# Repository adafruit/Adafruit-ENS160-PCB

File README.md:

## Adafruit ENS160 MOX Gas Sensor PCB

<a href="http://www.adafruit.com/products/5606"><br/>
Click here to purchase one from the Adafruit shop</a>

PCB files for the Adafruit ENS160 MOX Gas Sensor. 

Format is EagleCAD schematic and board layout
* https://www.adafruit.com/product/5606

### Description

*sniff* *sniff* ... do you smell that? No need to stick your nose into a carton of milk anymore, you can build a digital nose with the ENS160 Gas Sensor, a fully integrated MOX gas sensor. This is a very fine air quality sensor from the sensor experts at ScioSense, with I2C interfacing so you don't have to manage the heater and analog reading of a MOX sensor. It combines multiple metal-oxide sensing and heating elements on one chip to provide more detailed air quality signals.

The ENS160 is the replacement for the popular, but now-discontinued CCS811. It has similar functionality but does require all new driver code so be aware if you are updating from an original design with the CCS811 that some work is required to upgrade.

The ENS160 has a 'standard' hot-plate MOX sensor, as well as a small microcontroller that controls power to the plate, reads the analog voltage, and provides an I2C interface to read from. ScioSense provides an Arduino library with examples of reading the four raw resistance values and also the TVOC and eCO2 and a Python/CircuitPython library that can be used with Linux computers like the Raspberry Pi or our CircuitPython boards.

Please note, this sensor, like all VOC/gas sensors, has variability, and to get precise measurements you will want to calibrate it against known sources! That said, for general environmental sensors, it will give you a good idea of trends and comparison.

Another nice element to this sensor is the ability to set temperature and humidity compensation for better accuracy. An external humidity sensor is required and then the RH% is written over I2C to the sensor, so it can better calibrate the MOX sensor reading and reduce humidity/temperature-based variations.

Nice sensor right? So we made it easy for you to get right into your next project. The surface-mount sensor is soldered onto a custom-made PCB in the STEMMA QT form factor, making them easy to interface with. The STEMMA QT connectors on either side are compatible with the SparkFun Qwiic I2C connectors. This allows you to make solderless connections between your development board and the ENS160 or to chain it with a wide range of other sensors and accessories using a compatible cable. QT Cable is not included, but we have a variety in the shop

We’ve of course broken out all the pins to standard headers and added a 3.3V voltage regulator and level shifting to allow you to use it with either 3.3V or 5V systems such as the Arduino Uno, or Feather M4.

### License

Adafruit invests time and resources providing this open source design, please support Adafruit and open-source hardware by purchasing products from [Adafruit](https://www.adafruit.com)!

Designed by Limor Fried/Ladyada for Adafruit Industries.

Creative Commons Attribution/Share-Alike, all text above must be included in any redistribution. 
See license.txt for additional details.

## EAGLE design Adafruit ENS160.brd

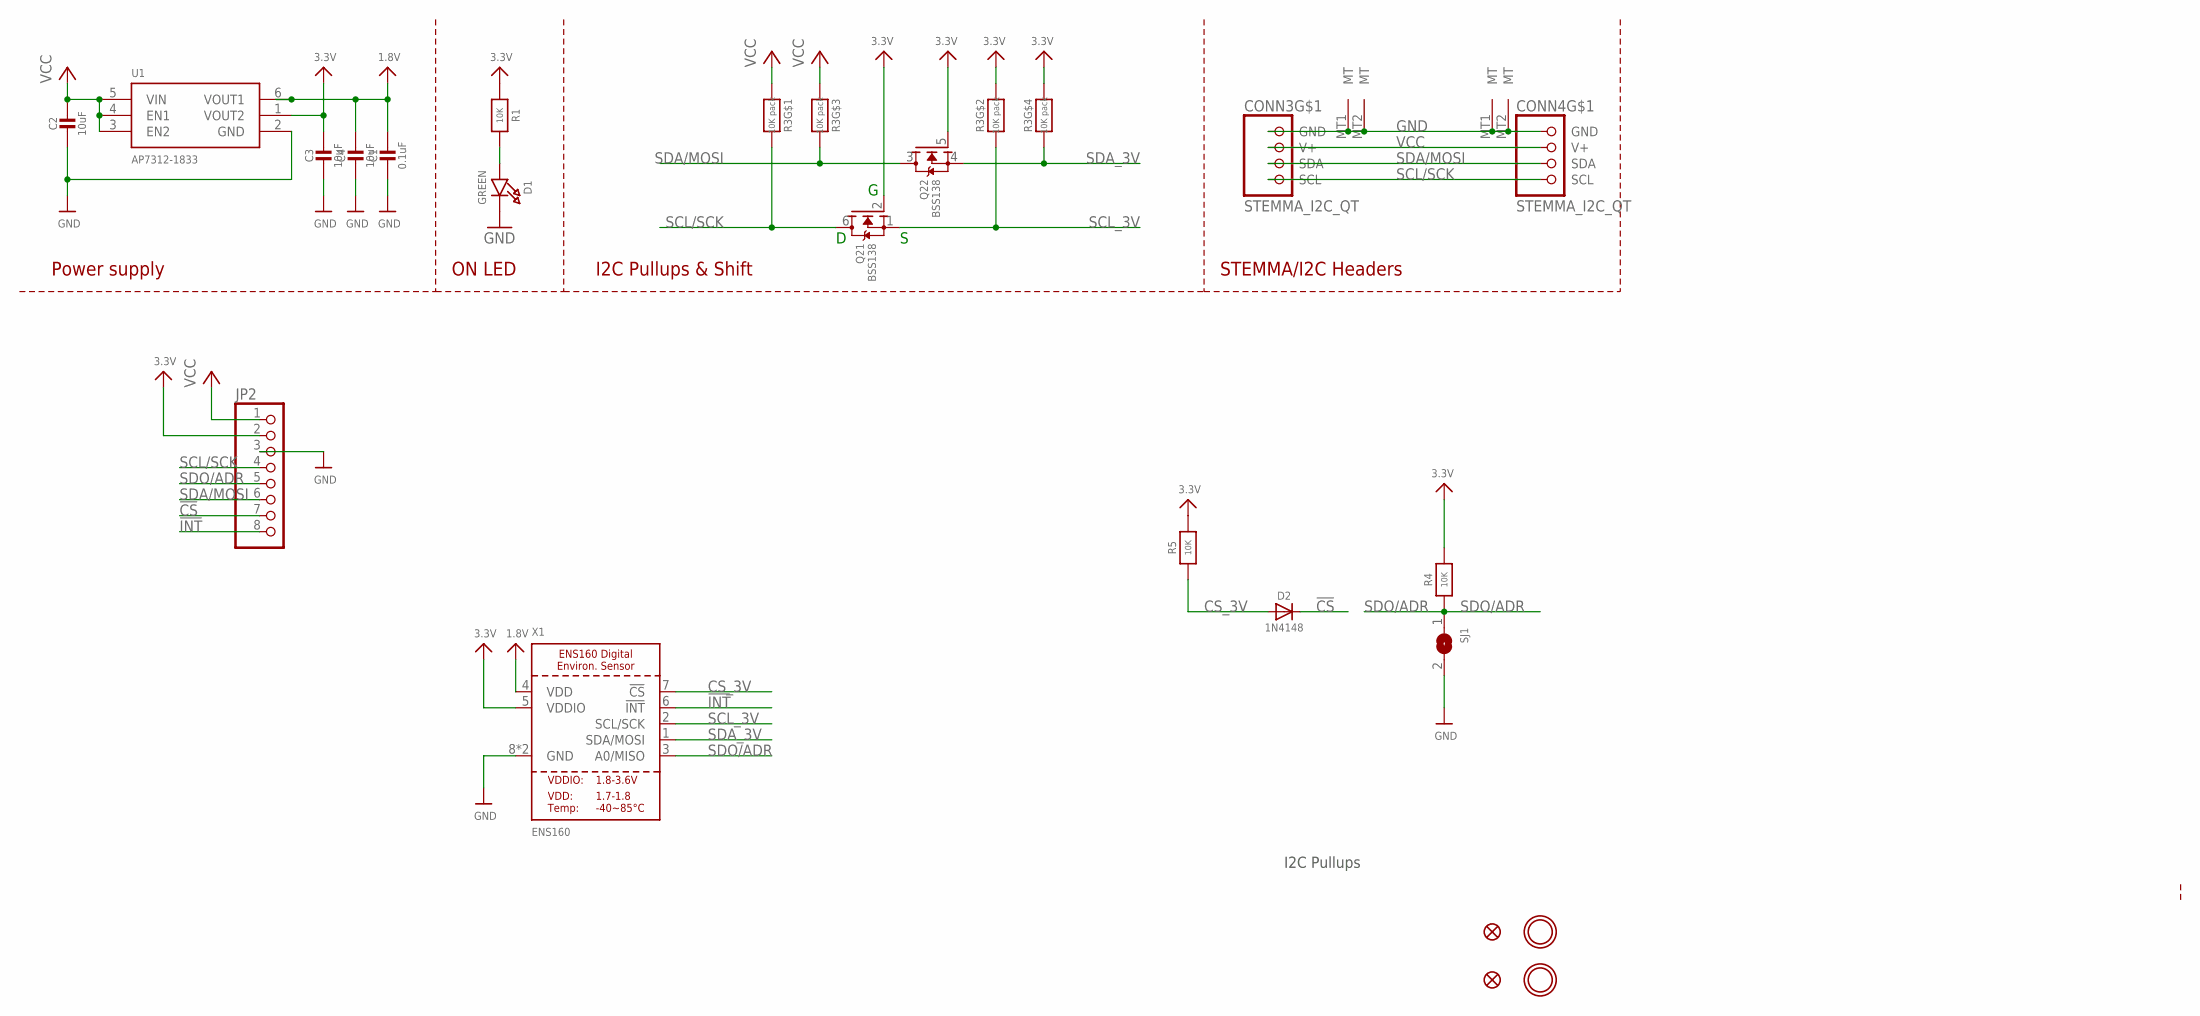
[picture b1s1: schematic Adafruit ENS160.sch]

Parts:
C1: 0.1uF; 0603-NO
C2, C3, C4: 10uF; 0805-NO
CONN3, CONN4: STEMMA_I2C_QT; JST_SH4
D1: GREEN; CHIPLED_0603_NOOUTLINE
D2: 1N4148; SOD-323
FID3, FID4: FIDUCIAL_1MM
JP2: HEADER-1X870MIL; 1X08_ROUND_70
Q2: BSS138; SOT363
R1, R4, R5: 10K; 0603-NO
R3: 10K pack; RESPACK_4X0603
SJ1: SOLDERJUMPER; SOLDERJUMPER_ARROW_NOPASTE
U1: AP7312-1833; SOT23-6
U$1, U$17: MOUNTINGHOLE2.5; MOUNTINGHOLE_2.5_PLATED
X1: ENS160

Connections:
1.8V: C1.1, C4.1, U1.6 (VOUT1), X1.4 (VDD)
3.3V: C3.1, JP2.2, Q2.2 (G), Q2.5 (G), R1.1, R3.2 (1), R3.4 (1), R4.2, R5.2, U1.1 (VOUT2), X1.5 (VDDIO)
!CS: D2.C, JP2.7
!INT: JP2.8, X1.6 (!INT)
CS_3V: D2.A, R5.1, X1.7 (!CS)
GND: C1.2, C2.2, C3.2, C4.2, CONN3.1 (GND), CONN3.MT1 (MT), CONN3.MT2 (MT), CONN4.1 (GND), CONN4.MT1 (MT), CONN4.MT2 (MT), D1.C, JP2.3, SJ1.2, U1.2 (GND), X1.8 (GND), X1.9 (GND)
unnamed: D1.A, R1.2
SCL/SCK: CONN3.4 (SCL), CONN4.4 (SCL), JP2.4, Q2.6 (D), R3.8 (2)
SCL_3V: Q2.1 (S), R3.7 (2), X1.2 (SCL/SCK)
SDA/MOSI: CONN3.3 (SDA), CONN4.3 (SDA), JP2.6, Q2.3 (D), R3.6 (2)
SDA_3V: Q2.4 (S), R3.5 (2), X1.1 (SDA/MOSI)
SDO/ADR: JP2.5, R4.1, SJ1.1, X1.3 (A0/MISO)
VCC: C2.1, CONN3.2 (V+), CONN4.2 (V+), JP2.1, R3.1, R3.3 (1), U1.3 (EN2), U1.4 (EN1), U1.5 (VIN)

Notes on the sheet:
I2C Pullups & Shift
STEMMA/I2C Headers
ON LED
Power supply
I2C Pullups

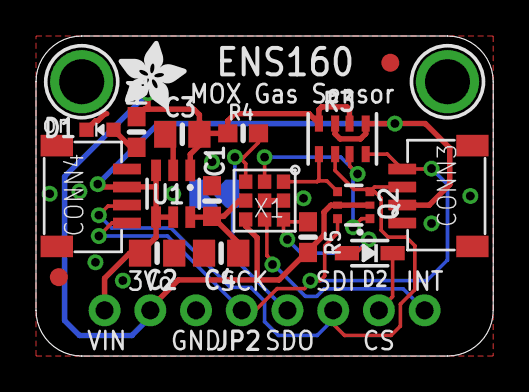
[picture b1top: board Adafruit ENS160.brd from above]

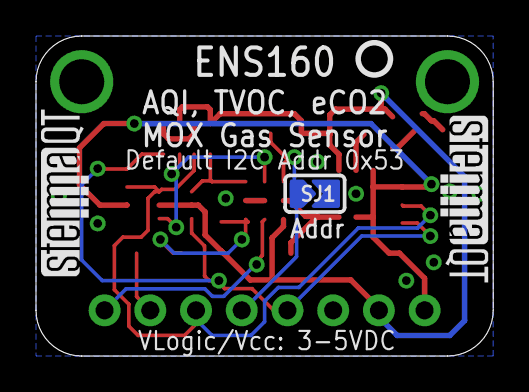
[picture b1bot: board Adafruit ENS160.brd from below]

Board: 2 copper layers, 25.4 x 17.8 mm, 25 parts (4 on the bottom side), 13 nets.

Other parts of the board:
U$20: ADAFRUIT_3.5MM
U$25: PCBFEAT-REV-040
U$30, U$31: STEMMAQT

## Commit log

2022-09-22 Adding cookiecutter output

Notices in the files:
parts and their libraries:
microbuilder: This work is placed in the public domain, and may be freely used for commercial and non-commercial work with the following conditions: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
